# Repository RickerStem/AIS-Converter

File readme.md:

KiCad files and docs for the AIS-Converter project.

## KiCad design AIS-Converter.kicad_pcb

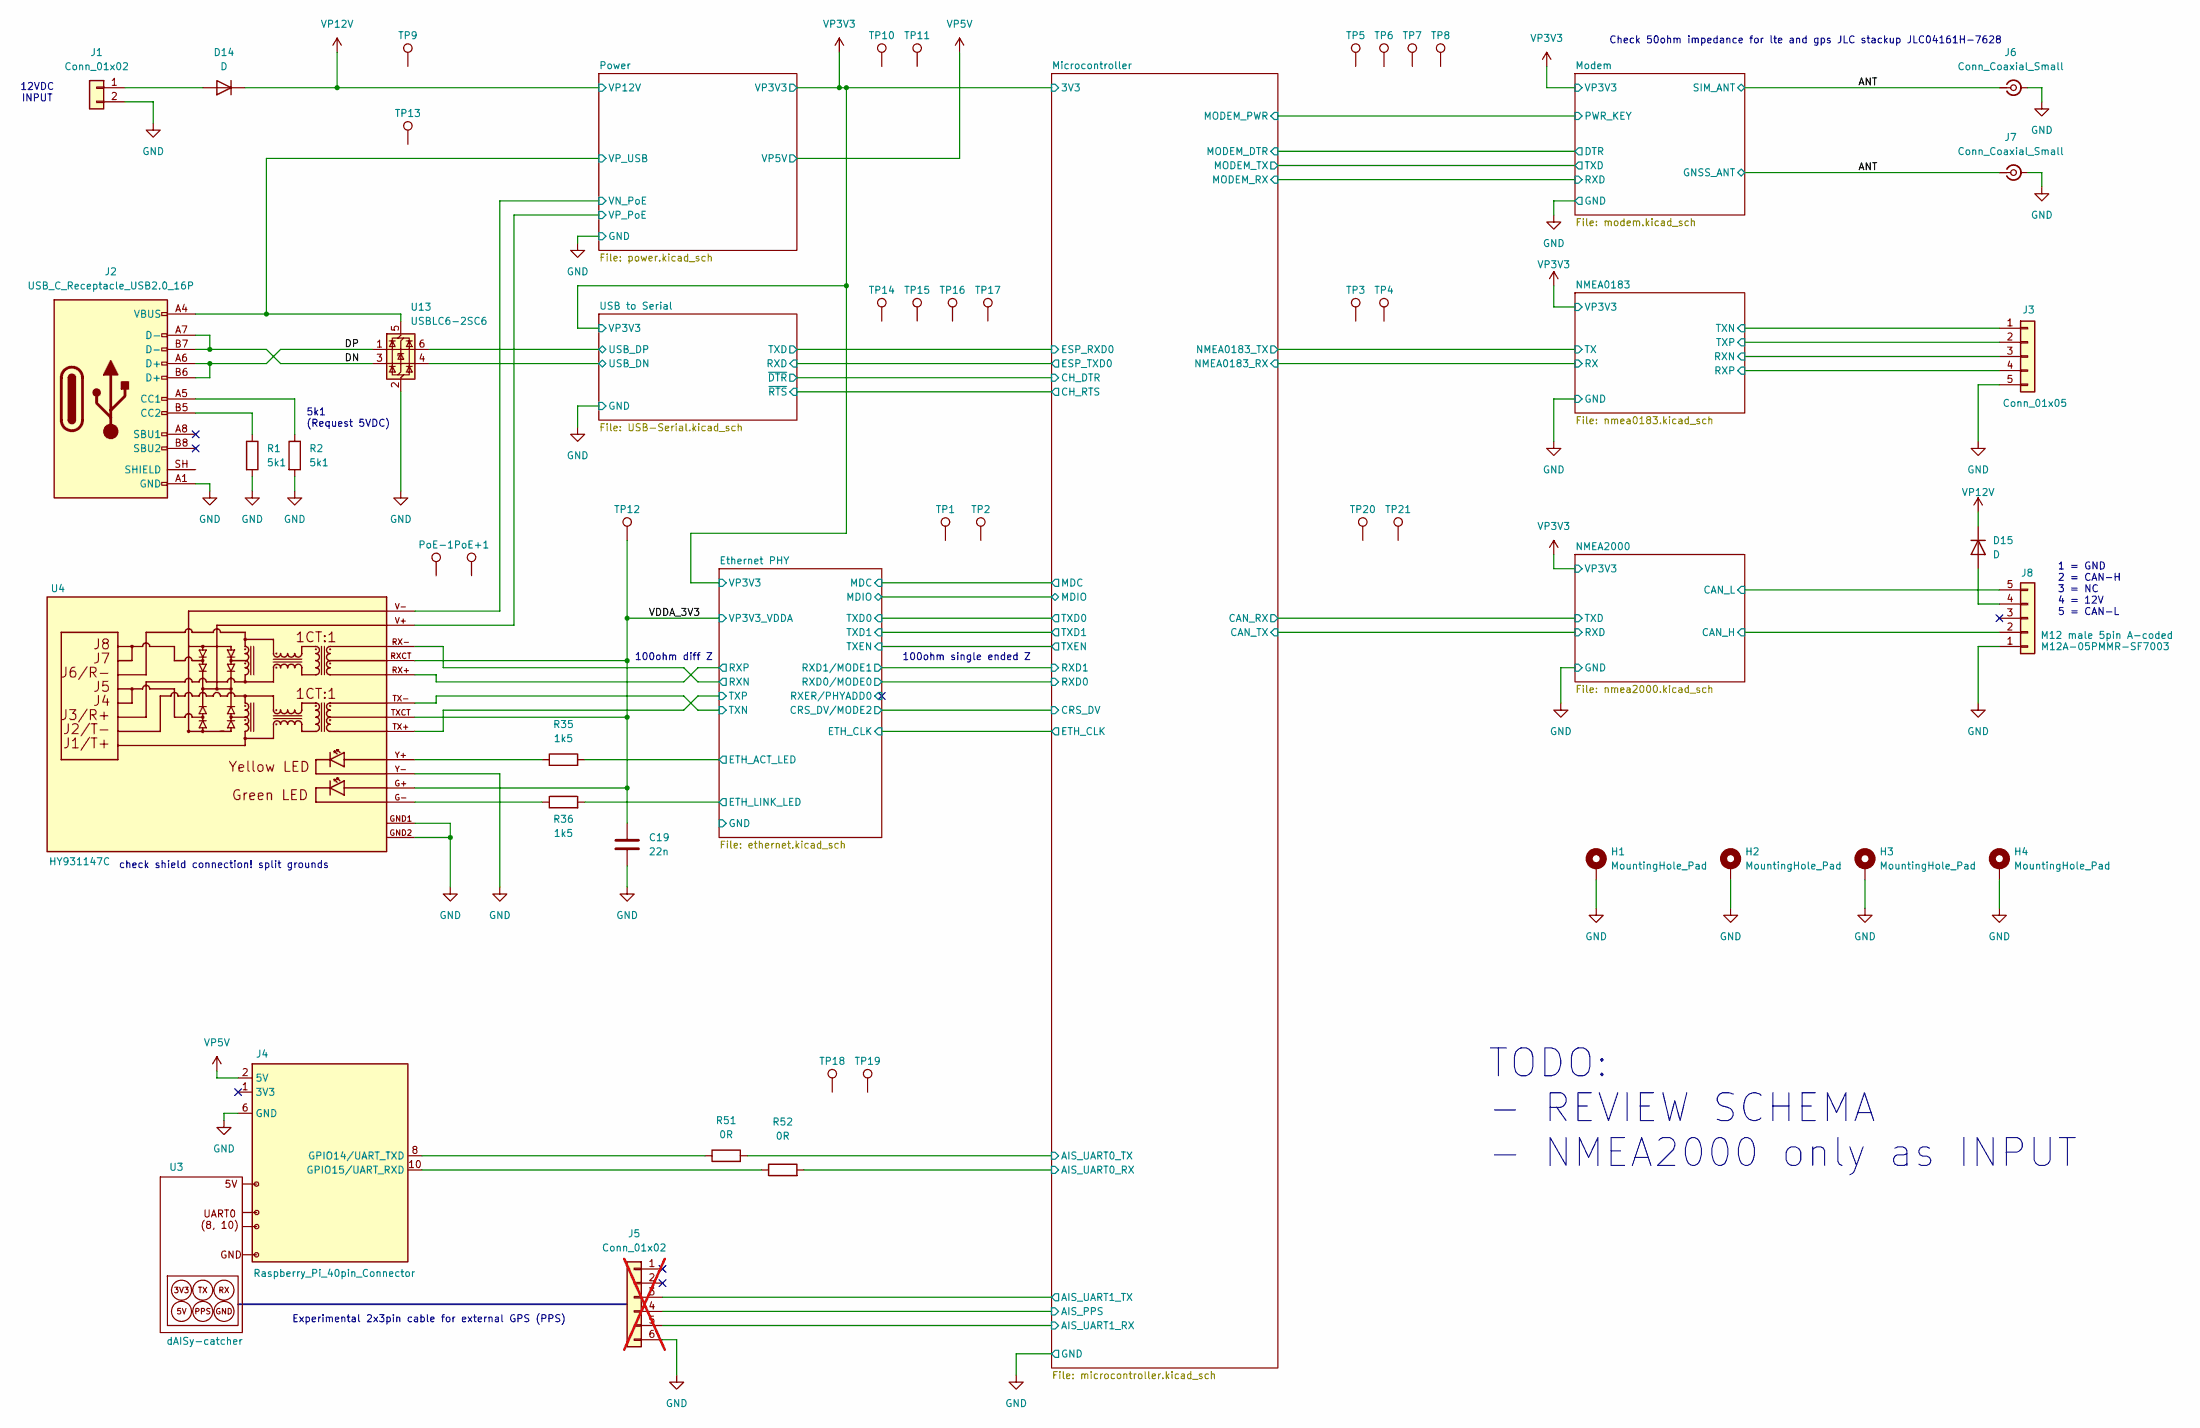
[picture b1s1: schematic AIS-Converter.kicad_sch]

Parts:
C19: 22n; C_0603_1608Metric
D14, D15: D; D_1206_3216Metric
H1, H2, H3, H4: MountingHole_Pad; MountingHole_3.2mm_M3_DIN965_Pad
J1: Conn_01x02; J_Wurth_WR-TBL_691322110002
J2: USB_C_Receptacle_USB2.0_16P; USB_C_Receptacle_Amphenol_124019772112A
J3: Conn_01x05; J_Wurth_WR-TBL_691322110005
J4: Raspberry_Pi_40pin_Connector; PinHeader_2x20_P2.54mm_Vertical
J5: Conn_01x02; PinSocket_2x03_P2.54mm_Vertical; not fitted
J6, J7: Conn_Coaxial_Small; SMA-KWE_C7498154
J8: M12A-05PMMR-SF7003; M12A05PMMRSF7003
PoE+1: TestPoint; TestPoint_Pad_D1.5mm
PoE-1: TestPoint; TestPoint_Pad_D1.5mm
R1, R2: 5k1; R_0805_2012Metric
R35, R36: 1k5; R_0603_1608Metric
R51, R52: 0R; R_0603_1608Metric
TP1, TP2, TP3, TP4, TP5, TP6, TP7, TP8, TP9, TP10, TP11, TP12, TP13, TP14, TP15, TP16, TP17, TP18, TP19, TP20, TP21: TestPoint; TestPoint_Pad_D1.5mm
U3: dAISy-catcher; dAISy-catcher-11mm
U4: HY931147C
U13: USBLC6-2SC6; SOT-23-6

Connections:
/ANT: J6.5 (In), J7.5 (In); also elsewhere on the board
/DN: J2.A7 (D-), J2.B7 (D-), U13.3 (I/O2)
/DP: J2.A6 (D+), J2.B6 (D+), U13.1 (I/O1)
/Ethernet PHY/ETH_ACT_LED: R35.2; also elsewhere on the board
/Ethernet PHY/ETH_LINK_LED: R36.2; also elsewhere on the board
/Ethernet PHY/RXN: U4.RX-; also elsewhere on the board
/Ethernet PHY/RXP: U4.RX+; also elsewhere on the board
/Ethernet PHY/TXN: U4.TX-; also elsewhere on the board
/Ethernet PHY/TXP: U4.TX+; also elsewhere on the board
/Microcontroller/AIS_PPS: J5.4
/Microcontroller/AIS_UART0_RX: R52.2; also elsewhere on the board
/Microcontroller/AIS_UART0_TX: R51.2; also elsewhere on the board
/Microcontroller/AIS_UART1_RX: J5.5
/Microcontroller/AIS_UART1_TX: J5.3
/NMEA0183/RXN: J3.3; also elsewhere on the board
/NMEA0183/RXP: J3.4; also elsewhere on the board
/NMEA0183/TXN: J3.1; also elsewhere on the board
/NMEA0183/TXP: J3.2; also elsewhere on the board
/NMEA2000/CAN_H: J8.2; also elsewhere on the board
/NMEA2000/CAN_L: J8.5; also elsewhere on the board
/Power/VN_PoE: U4.V-; also elsewhere on the board
/Power/VP_PoE: U4.V+; also elsewhere on the board
/Power/VP_USB: J2.A4 (VBUS), J2.A9 (VBUS), J2.B4 (VBUS), J2.B9 (VBUS), U13.5 (VBUS); also elsewhere on the board
/USB to Serial/USB_DN: U13.4 (I/O2); also elsewhere on the board
/USB to Serial/USB_DP: U13.6 (I/O1); also elsewhere on the board
/VDDA_3V3: C19.1, TP12.1 (1_1), U4.G+, U4.RXCT, U4.TXCT; also elsewhere on the board
GND: C19.2, H1.1 (1_1), H2.1 (1_1), H3.1 (1_1), H4.1 (1_1), J1.2, J2.A1 (GND), J2.A12 (GND), J2.B1 (GND), J2.B12 (GND), J3.5, J4.6 (GND), J4.9 (GND), J4.14 (GND), J4.20 (GND), J4.25 (GND), J4.30 (GND), J4.34 (GND), J4.39 (GND), J5.6, J6.1 (Ext), J6.2 (Ext), J6.3 (Ext), J6.4 (Ext), J7.1 (Ext), J7.2 (Ext), J7.3 (Ext), J7.4 (Ext), J8.1, R1.2, R2.2, U4.GND1, U4.GND2, U4.Y-, U13.2 (GND); also elsewhere on the board
unnamed: D14.2 (A), J1.1
unnamed: D15.2 (A), J8.4
unnamed: J2.A5 (CC1), R2.1
unnamed: J2.B5 (CC2), R1.1
unnamed: J4.8 (GPIO14/UART_TXD), R51.1
unnamed: J4.10 (GPIO15/UART_RXD), R52.1
unnamed: R35.1, U4.Y+
unnamed: R36.1, U4.G-
VP5V: J4.2 (5V), J4.4 (5V); also elsewhere on the board
VP12V: D14.1 (K), D15.1 (K)

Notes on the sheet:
12VDC INPUT
100ohm diff Z
check shield connection! split grounds
TODO: - REVIEW SCHEMA - NMEA2000 only as INPUT
Check 50ohm impedance for lte and gps JLC stackup JLC04161H-7628
Experimental 2x3pin cable for external GPS (PPS)
5k1 (Request 5VDC)
100ohm single ended Z
1 = GND 2 = CAN-H 3 = NC 4 = 12V 5 = CAN-L

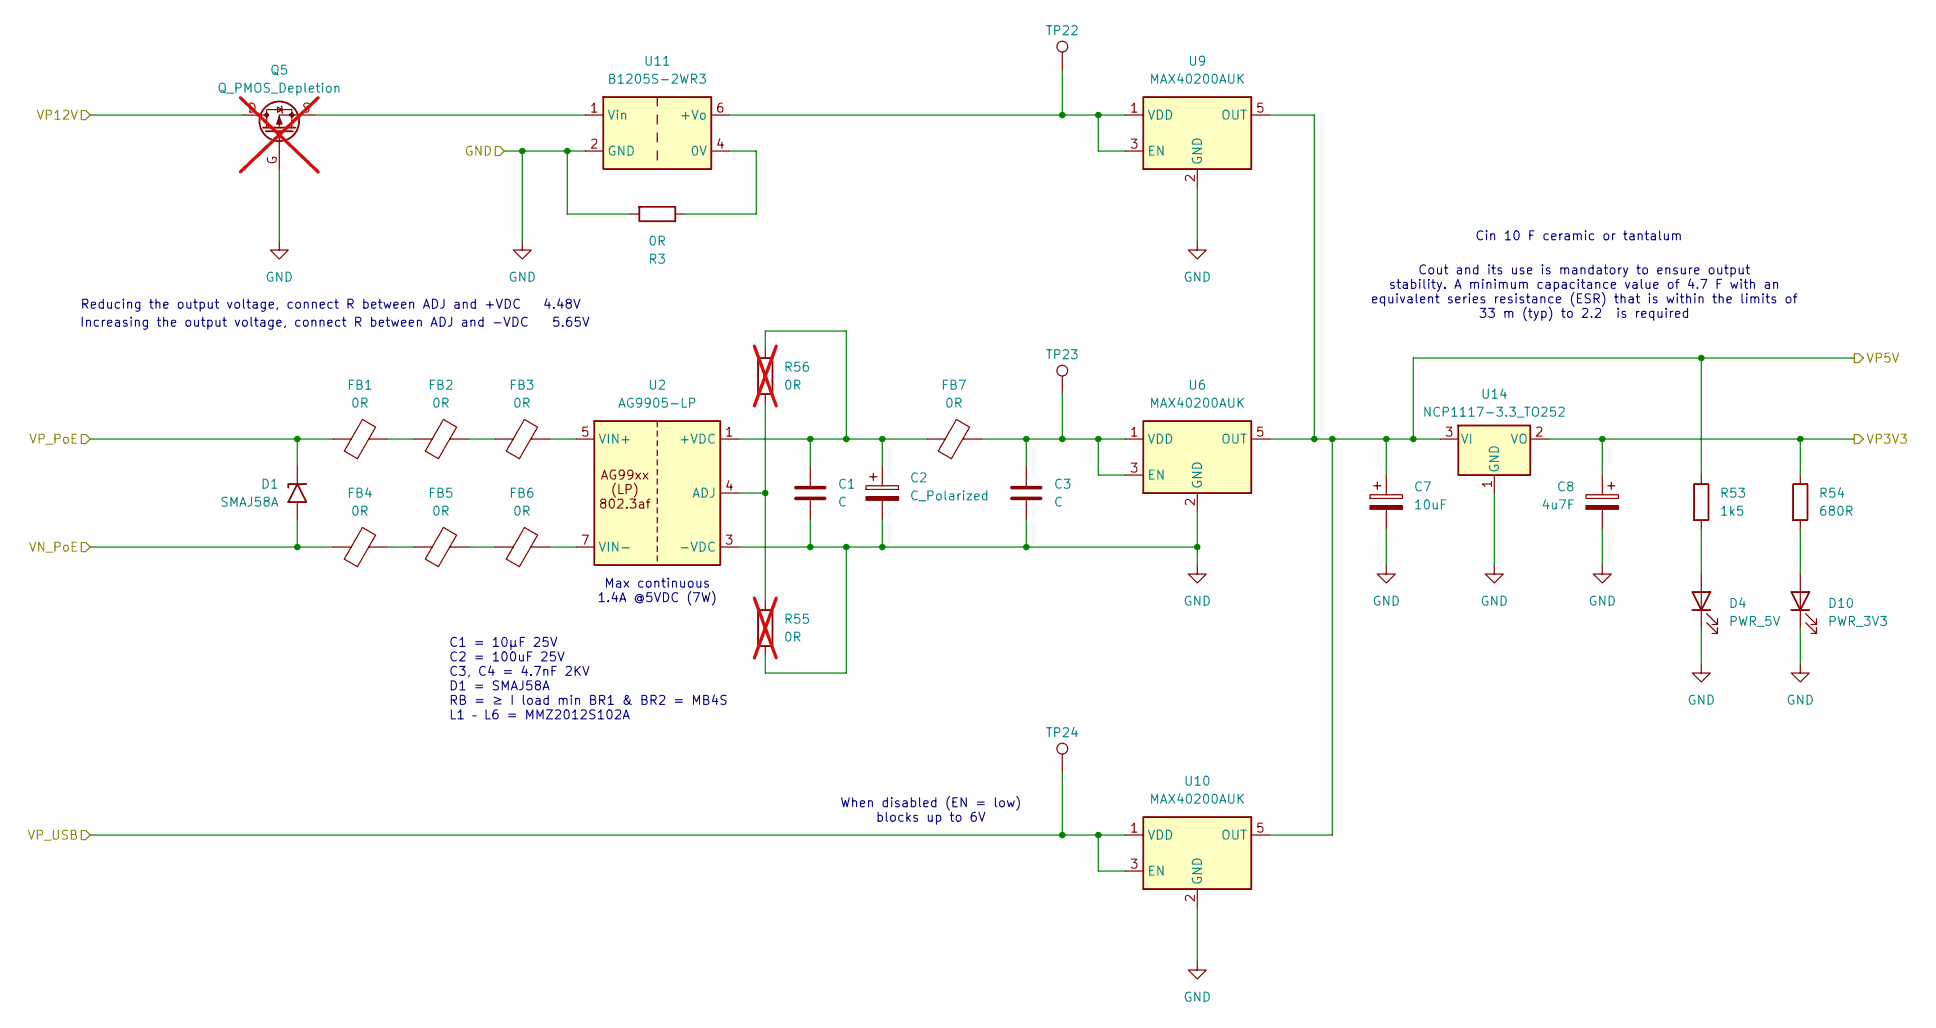
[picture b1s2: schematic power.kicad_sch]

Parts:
C1, C3: C; C_0603_1608Metric
C2: C_Polarized; C_0603_1608Metric
C7: 10uF; C_0603_1608Metric
C8: 4u7F; C_0603_1608Metric
D1: SMAJ58A; D_SMA
D4: PWR_5V; LED_0603_1608Metric
D10: PWR_3V3; LED_0603_1608Metric
FB1, FB2, FB3, FB4, FB5, FB6, FB7: 0R; L_0603_1608Metric
Q5: Q_PMOS_Depletion; not fitted
R3: 0R; R_0201_0603Metric
R53: 1k5; R_0603_1608Metric
R54: 680R; R_0603_1608Metric
R55, R56: 0R; R_0603_1608Metric; not fitted
TP22, TP23, TP24: TestPoint; TestPoint_Pad_D1.5mm
U2: AG9905-LP
U6, U9, U10: MAX40200AUK; SOT-23-5
U11: B1205S-2WR3
U14: NCP1117-3.3_TO252; TO-252-2

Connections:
/Power/VN_PoE: D1.2 (A2), FB4.1; also elsewhere on the board
/Power/VP_PoE: D1.1 (A1), FB1.1; also elsewhere on the board
/Power/VP_USB: TP24.1 (1_1), U10.1 (VDD), U10.3 (EN); also elsewhere on the board
GND: C1.2, C2.2, C3.2, C7.2, C8.2, D4.1 (K), D10.1 (K), Q5.G, R3.2, R55.2, U2.3 (-VDC), U6.2 (GND), U9.2 (GND), U10.2 (GND), U11.2 (GND), U14.1 (GND); also elsewhere on the board
unnamed: C1.1, C2.1, FB7.1, R56.1, U2.1 (+VDC), U2.2 (+VDC)
unnamed: D4.2 (A), R53.2
unnamed: D10.2 (A), R54.2
unnamed: FB1.2, FB2.1
unnamed: FB2.2, FB3.1
unnamed: FB4.2, FB5.1
unnamed: FB5.2, FB6.1
unnamed: R55.1, R56.2, U2.4 (ADJ)
unnamed: C3.1, FB7.2, TP23.1 (1_1), U6.1 (VDD), U6.3 (EN)
unnamed: R3.1, U11.4 (0V)
unnamed: TP22.1 (1_1), U9.1 (VDD), U9.3 (EN), U11.6 (+Vo)
unnamed: Q5.S, U11.1 (Vin)
VIN+: FB3.2, U2.5 (VIN+), U2.6 (VIN+)
VIN-: FB6.2, U2.7 (VIN-), U2.8 (VIN-)
VP3V3: C8.1, R54.1, U14.2 (VO); also elsewhere on the board
VP5V: C7.1, R53.1, U6.5 (OUT), U9.5 (OUT), U10.5 (OUT), U14.3 (VI); also elsewhere on the board

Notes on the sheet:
4.48V
5.65V
Max continuous 1.4A @5VDC (7W)
Cin 10 F ceramic or tantalum
Cout and its use is mandatory to ensure output stability. A minimum capacitance value of 4.7 F with an equivalent series resistance (ESR) that is within the limits of 33 m (typ) to 2.2 is required
Increasing the output voltage, connect R between ADJ and -VDC
When disabled (EN = low) blocks up to 6V
C1 = 10µF 25V C2 = 100uF 25V C3, C4 = 4.7nF 2KV D1 = SMAJ58A RB = ≥ I load min BR1 & BR2 = MB4S L1 – L6 = MMZ2012S102A
Reducing the output voltage, connect R between ADJ and +VDC

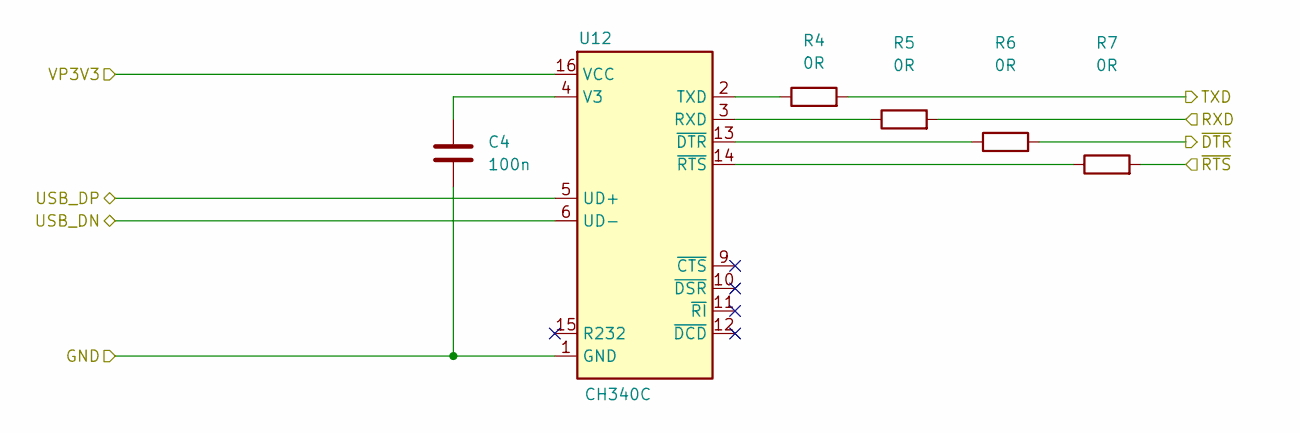
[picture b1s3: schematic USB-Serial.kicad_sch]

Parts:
C4: 100n; C_0603_1608Metric
R4, R5, R6, R7: 0R; R_0603_1608Metric
U12: CH340C; SOIC-16_3.9x9.9mm_P1.27mm

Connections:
/Microcontroller/CH_DTR: R6.2; also elsewhere on the board
/Microcontroller/CH_RTS: R7.2; also elsewhere on the board
/Microcontroller/ESP_RXD0: R4.2; also elsewhere on the board
/Microcontroller/ESP_TXD0: R5.2; also elsewhere on the board
/USB to Serial/USB_DN: U12.6 (UD-); also elsewhere on the board
/USB to Serial/USB_DP: U12.5 (UD+); also elsewhere on the board
GND: C4.2, U12.1 (GND); also elsewhere on the board
unnamed: R5.1, U12.3 (RXD)
unnamed: R4.1, U12.2 (TXD)
unnamed: C4.1, U12.4 (V3)
unnamed: R6.1, U12.13 (~DTR)
unnamed: R7.1, U12.14 (~RTS)
VP3V3: U12.16 (VCC); also elsewhere on the board

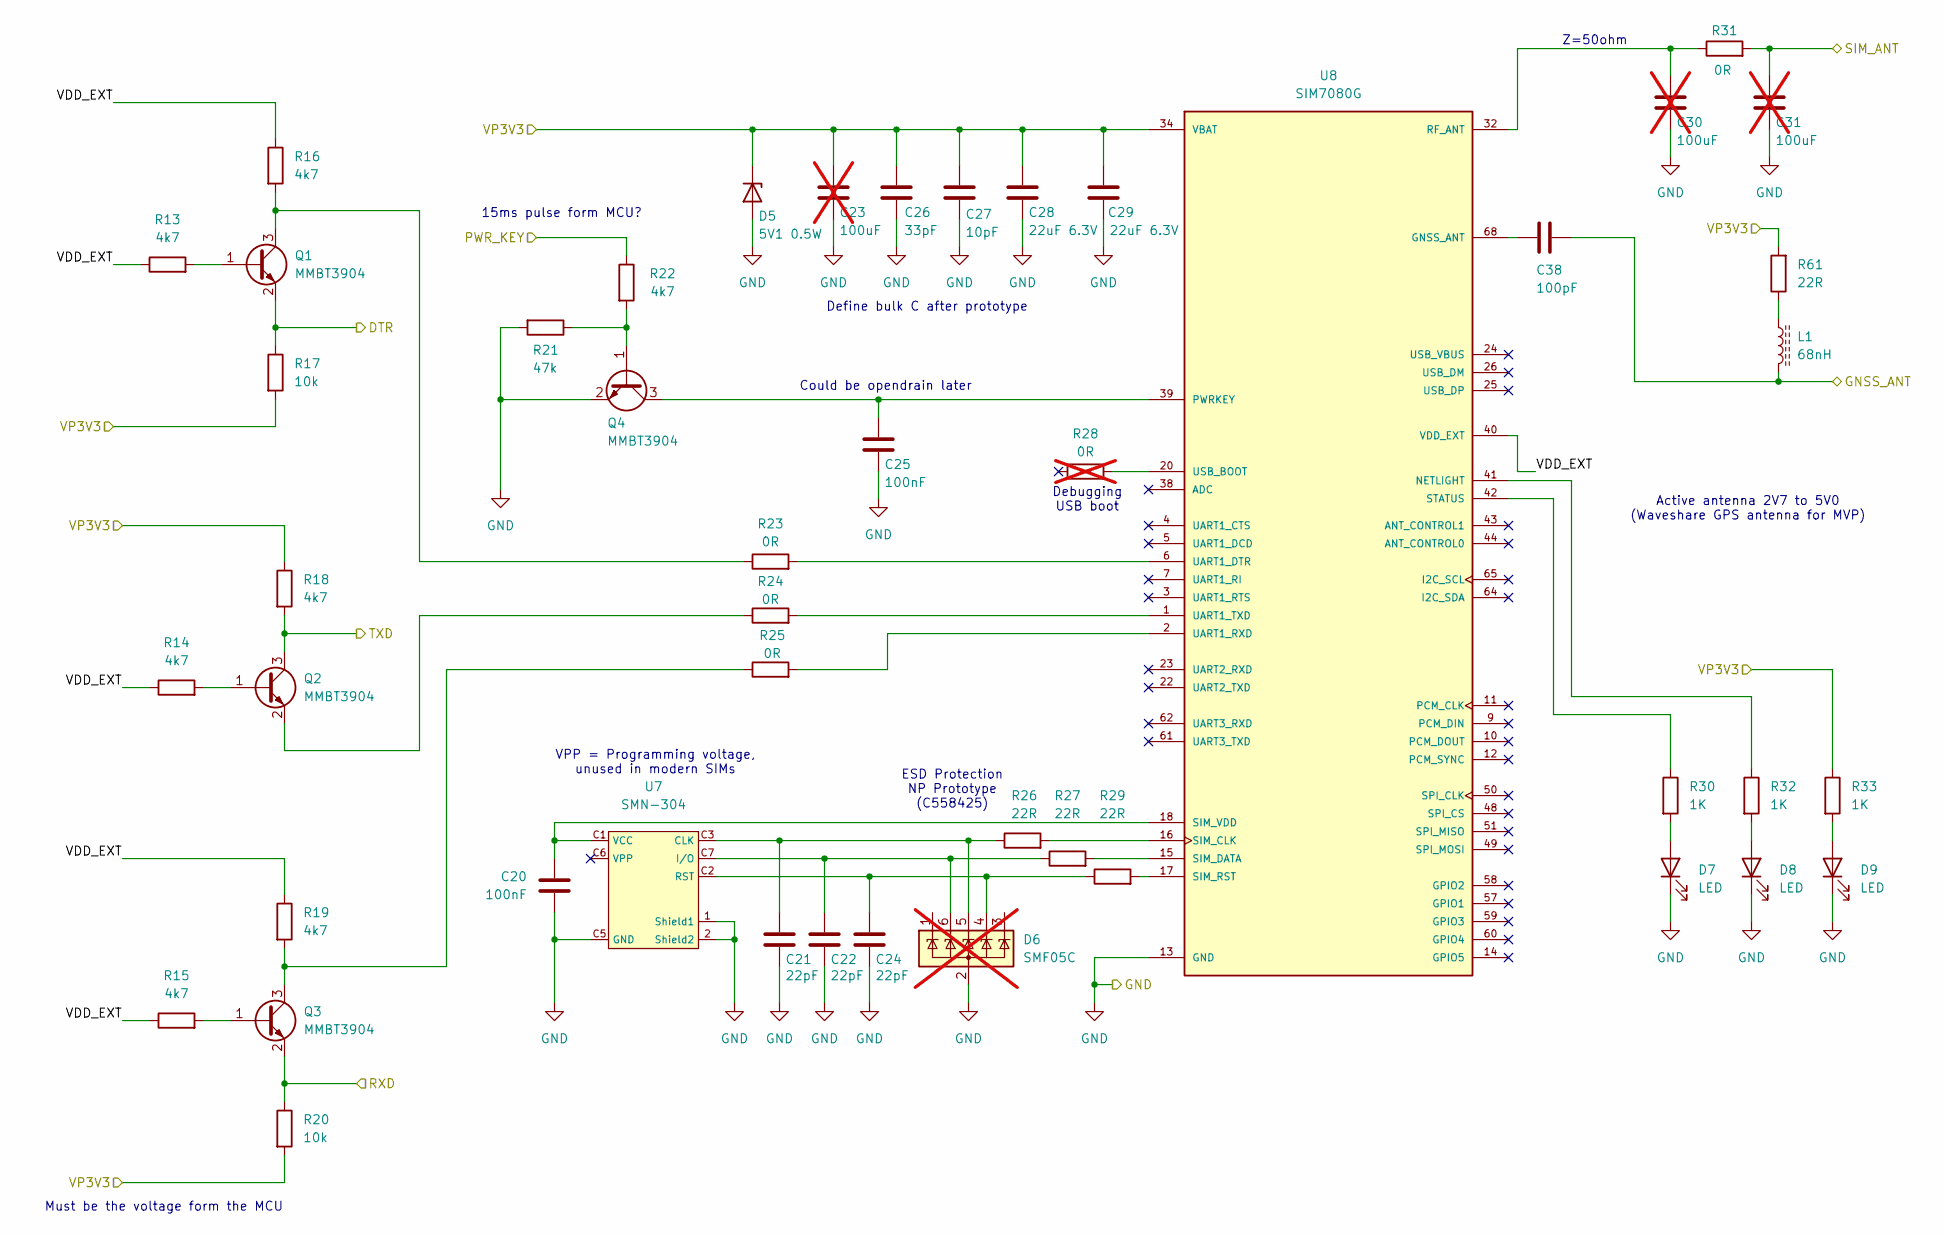
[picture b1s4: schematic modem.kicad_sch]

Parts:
C20, C25: 100nF; C_0603_1608Metric
C21, C22, C24: 22pF; C_0603_1608Metric
C23, C30, C31: 100uF; C_0603_1608Metric; not fitted
C26: 33pF; C_0603_1608Metric
C27: 10pF; C_0603_1608Metric
C28, C29: 22uF 6.3V; C_0603_1608Metric
C38: 100pF; C_0603_1608Metric
D5: 5V1 0.5W; D_MiniMELF
D6: SMF05C; SOT-363_SC-70-6; not fitted
D7, D8, D9: LED; LED_0603_1608Metric
L1: 68nH; L_0603_1608Metric
Q1, Q2, Q3, Q4: MMBT3904; SOT-23
R13, R14, R15, R16, R18, R19, R22: 4k7; R_0603_1608Metric
R17, R20: 10k; R_0603_1608Metric
R21: 47k; R_0603_1608Metric
R23, R24, R25, R31: 0R; R_0603_1608Metric
R26, R27, R29, R61: 22R; R_0603_1608Metric
R28: 0R; R_0603_1608Metric; not fitted
R30, R32, R33: 1K; R_0603_1608Metric
U7: SMN-304; LCSC C266889
U8: SIM7080G; XCVR_SIM7080G; PARTREV 1.04

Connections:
/ANT: C31.1, C38.1, L1.2, R31.2; also elsewhere on the board
/Microcontroller/MODEM_DTR: Q1.2 (E), R17.1; also elsewhere on the board
/Microcontroller/MODEM_PWR: R22.1; also elsewhere on the board
/Microcontroller/MODEM_RX: Q3.2 (E), R20.1; also elsewhere on the board
/Microcontroller/MODEM_TX: Q2.3 (C), R18.2; also elsewhere on the board
/Modem/VDD_EXT: R13.1, R14.1, R15.1, R16.1, R19.1, U8.40 (VDD_EXT)
GND: C20.2, C21.2, C22.2, C23.2, C24.2, C25.2, C26.2, C27.2, C28.2, C29.2, C30.2, C31.2, D5.2 (A), D6.2 (A), D7.1 (K), D8.1 (K), D9.1 (K), Q4.2 (E), R21.2, U7.1 (Shield1), U7.2 (Shield2), U7.C5 (GND), U8.8 (GND), U8.13 (GND), U8.19 (GND), U8.21 (GND), U8.27 (GND), U8.30 (GND), U8.31 (GND), U8.33 (GND), U8.36 (GND), U8.37 (GND), U8.45 (GND), U8.63 (GND), U8.66 (GND), U8.67 (GND), U8.69 (GND), U8.70 (GND), U8.71 (GND), U8.72 (GND), U8.73 (GND), U8.74 (GND), U8.75 (GND), U8.76 (GND), U8.77 (GND); also elsewhere on the board
unnamed: D7.2 (A), R30.2
unnamed: D8.2 (A), R32.2
unnamed: D9.2 (A), R33.2
unnamed: L1.1, R61.1
unnamed: Q1.1 (B), R13.2
unnamed: Q1.3 (C), R16.2, R23.1
unnamed: Q2.1 (B), R14.2
unnamed: Q2.2 (E), R24.1
unnamed: Q3.1 (B), R15.2
unnamed: Q3.3 (C), R19.2, R25.1
unnamed: Q4.1 (B), R21.1, R22.2
unnamed: C25.1, Q4.3 (C), U8.39 (PWRKEY)
unnamed: C21.1, D6.5 (K), R26.1, U7.C3 (CLK)
unnamed: C22.1, D6.6 (K), R27.1, U7.C7 (I/O)
unnamed: C24.1, D6.4 (K), R29.1, U7.C2 (RST)
unnamed: C20.1, U7.C1 (VCC), U8.18 (SIM_VDD)
unnamed: C38.2, U8.68 (GNSS_ANT)
unnamed: R32.1, U8.41 (NETLIGHT)
unnamed: C30.1, R31.1, U8.32 (RF_ANT)
unnamed: R26.2, U8.16 (SIM_CLK)
unnamed: R27.2, U8.15 (SIM_DATA)
unnamed: R29.2, U8.17 (SIM_RST)
unnamed: R30.1, U8.42 (STATUS)
unnamed: R23.2, U8.6 (UART1_DTR)
unnamed: R25.2, U8.2 (UART1_RXD)
unnamed: R24.2, U8.1 (UART1_TXD)
unnamed: R28.2 (~_2), U8.20 (USB_BOOT)
VP3V3: C23.1, C26.1, C27.1, C28.1, C29.1, D5.1 (K), R17.2, R18.1, R20.2, R33.1, R61.2, U8.34 (VBAT), U8.35 (VBAT); also elsewhere on the board

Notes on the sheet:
Define bulk C after prototype
VPP = Programming voltage, unused in modern SIMs
Debugging USB boot
ESD Protection NP Prototype (C558425)
Must be the voltage form the MCU
Z=50ohm
Could be opendrain later
15ms pulse form MCU?
Active antenna 2V7 to 5V0 (Waveshare GPS antenna for MVP)

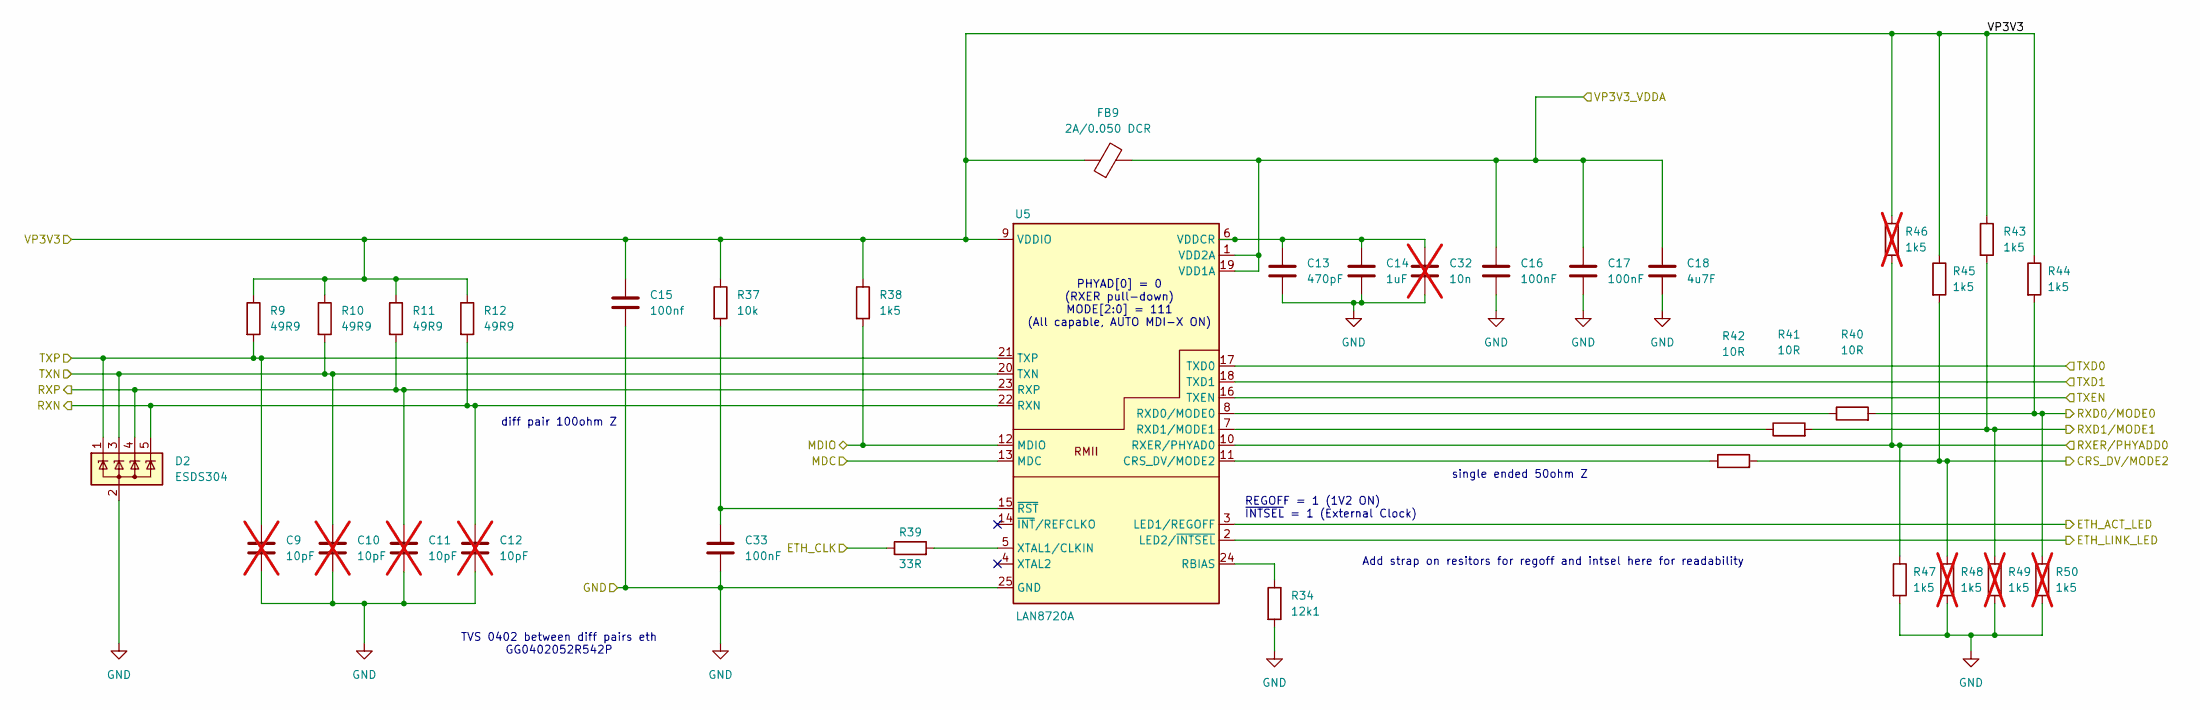
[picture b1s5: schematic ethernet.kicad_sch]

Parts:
C9, C10, C11, C12: 10pF; C_0402_1005Metric; not fitted
C13: 470pF; C_0603_1608Metric
C14: 1uF; C_0603_1608Metric
C15: 100nf; C_0603_1608Metric
C16, C17, C33: 100nF; C_0603_1608Metric
C18: 4u7F; C_0603_1608Metric
C32: 10n; C_0603_1608Metric; not fitted
D2: ESDS304; SOT-23-5
FB9: 2A/0.050 DCR; L_0603_1608Metric
R9, R10, R11, R12: 49R9; R_0402_1005Metric
R34: 12k1; R_0402_1005Metric
R37: 10k; R_0603_1608Metric
R38, R43, R44, R45, R47: 1k5; R_0603_1608Metric
R39: 33R; R_0603_1608Metric
R40, R41, R42: 10R; R_0402_1005Metric
R46, R48, R49, R50: 1k5; R_0603_1608Metric; not fitted
U5: LAN8720A; VQFN-24-1EP_4x4mm_P0.5mm_EP2.5x2.5mm_ThermalVias

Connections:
/Ethernet PHY/CRS_DV/MODE2: R42.2, R45.2, R48.1; also elsewhere on the board
/Ethernet PHY/ETH_ACT_LED: U5.3 (LED1/REGOFF); also elsewhere on the board
/Ethernet PHY/ETH_CLK: R39.1; also elsewhere on the board
/Ethernet PHY/ETH_LINK_LED: U5.2 (LED2/~INTSEL); also elsewhere on the board
/Ethernet PHY/MDC: U5.13 (MDC); also elsewhere on the board
/Ethernet PHY/MDIO: R38.2, U5.12 (MDIO); also elsewhere on the board
/Ethernet PHY/RXD0/MODE0: R40.2, R44.2, R50.1; also elsewhere on the board
/Ethernet PHY/RXD1/MODE1: R41.2, R43.2, R49.1; also elsewhere on the board
/Ethernet PHY/RXER/PHYADD0: R46.2, R47.1, U5.10 (RXER/PHYAD0)
/Ethernet PHY/RXN: C12.1, D2.5 (K), R12.2, U5.22 (RXN); also elsewhere on the board
/Ethernet PHY/RXP: C11.1, D2.4 (K), R11.2, U5.23 (RXP); also elsewhere on the board
/Ethernet PHY/TXD0: U5.17 (TXD0); also elsewhere on the board
/Ethernet PHY/TXD1: U5.18 (TXD1); also elsewhere on the board
/Ethernet PHY/TXEN: U5.16 (TXEN); also elsewhere on the board
/Ethernet PHY/TXN: C10.1, D2.3 (K), R10.2, U5.20 (TXN); also elsewhere on the board
/Ethernet PHY/TXP: C9.1, D2.1 (K), R9.2, U5.21 (TXP); also elsewhere on the board
/VDDA_3V3: C16.1, C17.1, C18.1, FB9.2, U5.1 (VDD2A), U5.19 (VDD1A); also elsewhere on the board
GND: C9.2, C10.2, C11.2, C12.2, C13.2, C14.2, C15.2, C16.2, C17.2, C18.2, C32.2, C33.2, D2.2 (A), R34.2, R47.2, R48.2, R49.2, R50.2, U5.25 (GND); also elsewhere on the board
unnamed: R42.1, U5.11 (CRS_DV/MODE2)
unnamed: R34.1, U5.24 (RBIAS)
unnamed: R40.1, U5.8 (RXD0/MODE0)
unnamed: R41.1, U5.7 (RXD1/MODE1)
unnamed: C13.1, C14.1, C32.1, U5.6 (VDDCR)
unnamed: R39.2, U5.5 (XTAL1/CLKIN)
unnamed: C33.1, R37.2, U5.15 (~RST)
VP3V3: C15.1, FB9.1, R9.1, R10.1, R11.1, R12.1, R37.1, R38.1, R43.1, R44.1, R45.1, R46.1, U5.9 (VDDIO); also elsewhere on the board

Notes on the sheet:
single ended 50ohm Z
PHYAD[0] = 0 (RXER pull-down) MODE[2:0] = 111 (All capable, AUTO MDI-X ON)
diff pair 100ohm Z
TVS 0402 between diff pairs eth GG0402052R542P
Add strap on resitors for regoff and intsel here for readability
REGOFF = 1 (1V2 ON) ~{INTSEL} = 1 (External Clock)

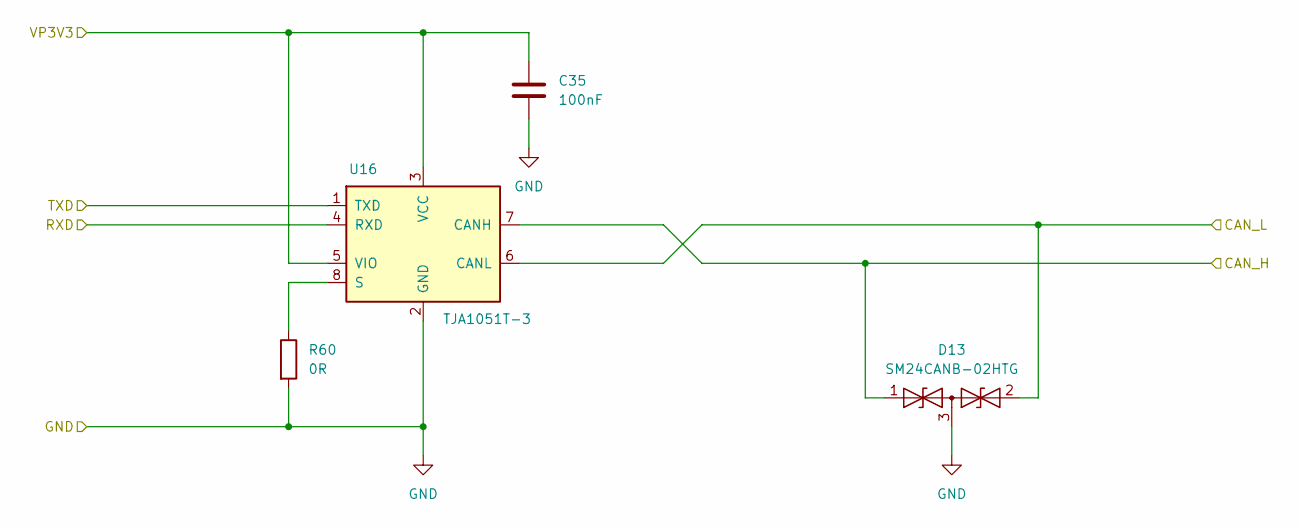
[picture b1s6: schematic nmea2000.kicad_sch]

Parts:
C35: 100nF; C_0603_1608Metric
D13: SM24CANB-02HTG; SOT-23
R60: 0R; R_0603_1608Metric
U16: TJA1051T-3; SOIC-8_3.9x4.9mm_P1.27mm

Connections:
/Microcontroller/CAN_RX: U16.1 (TXD); also elsewhere on the board
/Microcontroller/CAN_TX: U16.4 (RXD); also elsewhere on the board
/NMEA2000/CAN_H: D13.1 (A1), U16.7 (CANH); also elsewhere on the board
/NMEA2000/CAN_L: D13.2 (A2), U16.6 (CANL); also elsewhere on the board
GND: C35.2, D13.3 (common), R60.2, U16.2 (GND); also elsewhere on the board
unnamed: R60.1, U16.8 (S)
VP3V3: C35.1, U16.3 (VCC), U16.5 (VIO); also elsewhere on the board

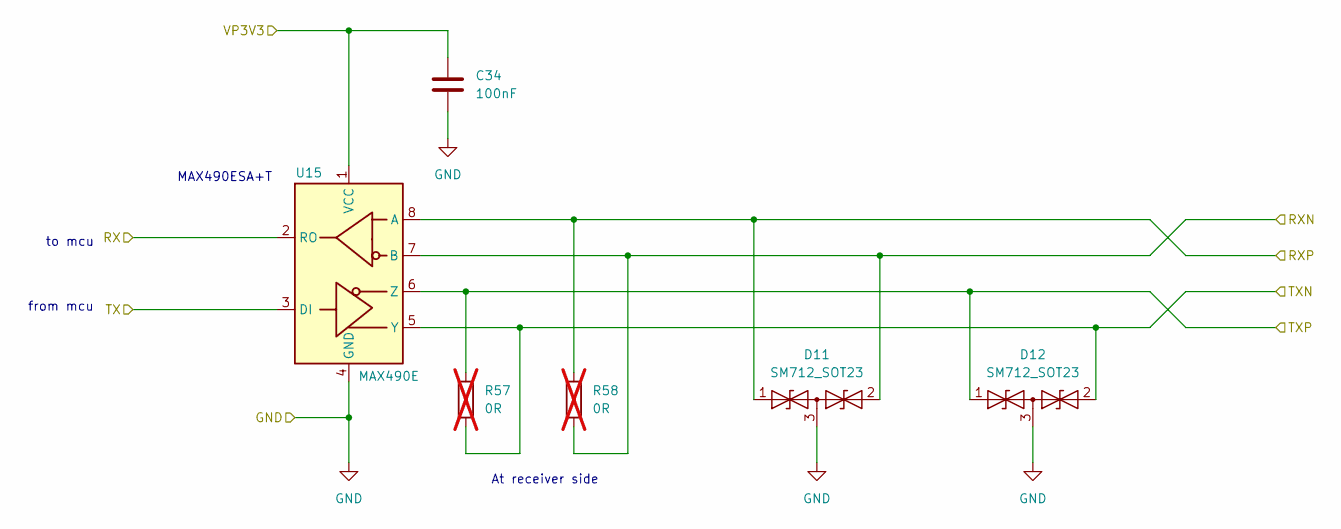
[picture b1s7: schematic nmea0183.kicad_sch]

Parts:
C34: 100nF; C_0603_1608Metric
D11, D12: SM712_SOT23; SOT-23
R57, R58: 0R; R_0603_1608Metric; not fitted
U15: MAX490E; SOIC-8_3.9x4.9mm_P1.27mm

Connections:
/Microcontroller/NMEA0183_RX: U15.2 (RO); also elsewhere on the board
/Microcontroller/NMEA0183_TX: U15.3 (DI); also elsewhere on the board
/NMEA0183/RXN: D11.2 (A2), R58.2, U15.7 (B); also elsewhere on the board
/NMEA0183/RXP: D11.1 (A1), R58.1, U15.8 (A); also elsewhere on the board
/NMEA0183/TXN: D12.2 (A2), R57.2, U15.5 (Y); also elsewhere on the board
/NMEA0183/TXP: D12.1 (A1), R57.1, U15.6 (Z); also elsewhere on the board
GND: C34.2, D11.3 (common), D12.3 (common), U15.4 (GND); also elsewhere on the board
VP3V3: C34.1, U15.1 (VCC); also elsewhere on the board

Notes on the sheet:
from mcu
At receiver side
to mcu
MAX490ESA+T

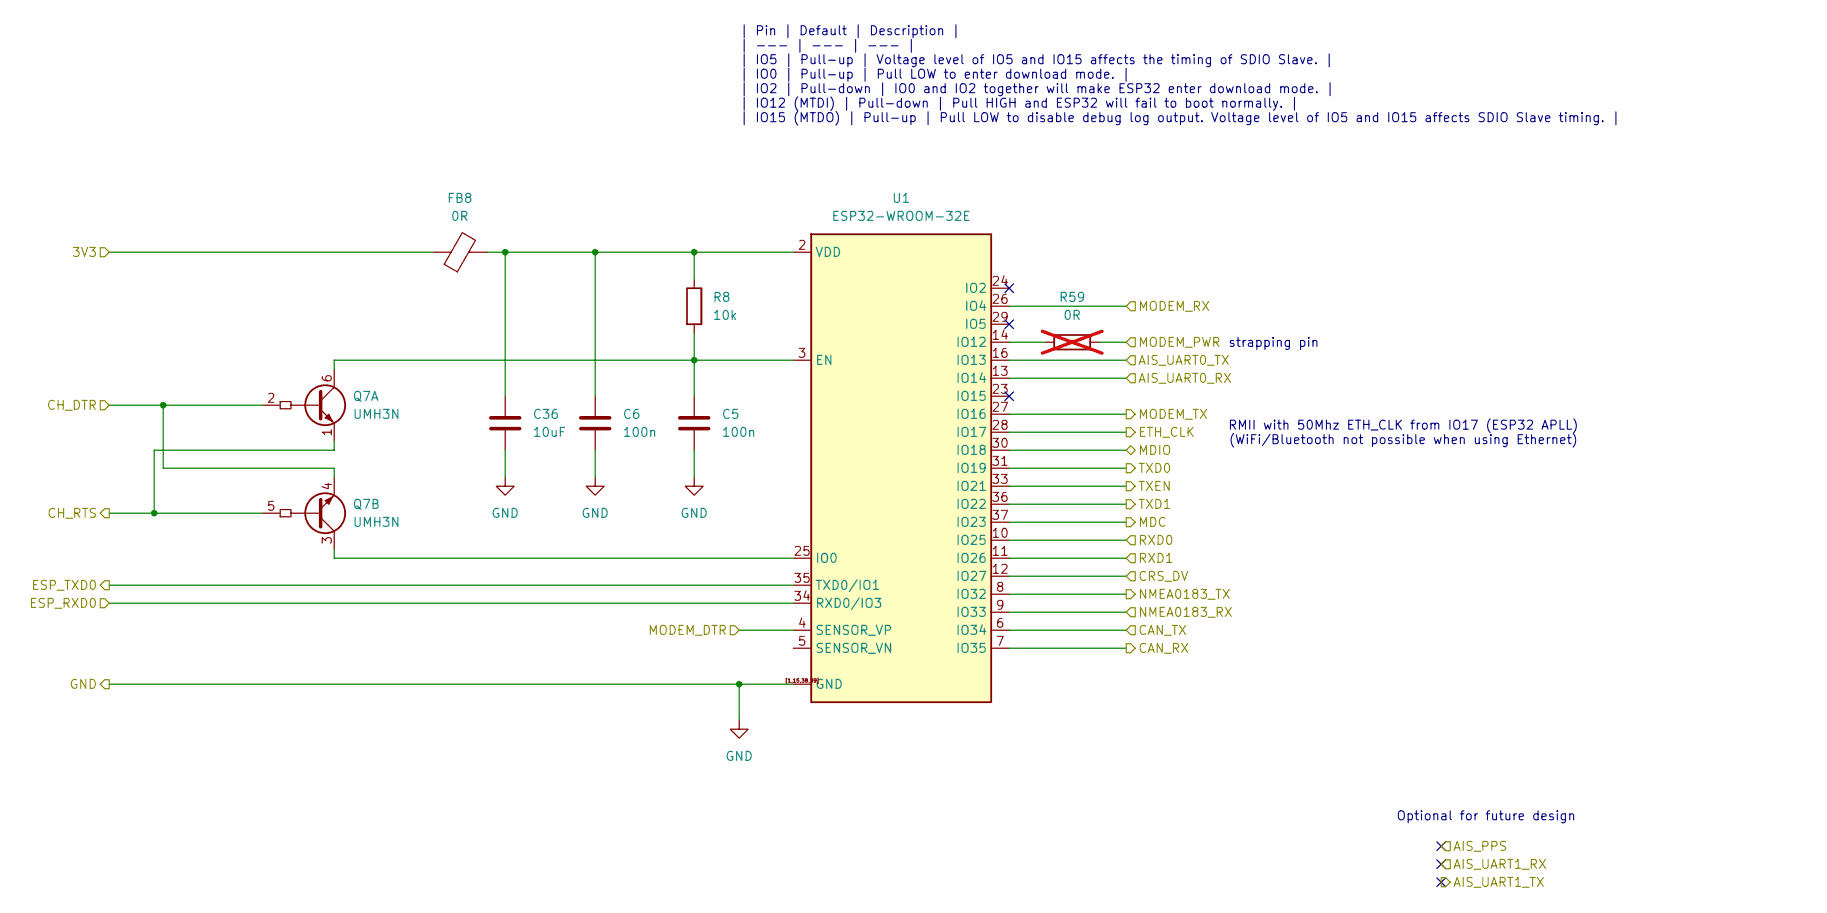
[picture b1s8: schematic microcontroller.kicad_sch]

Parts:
C5, C6: 100n; C_0603_1608Metric
C36: 10uF; C_0603_1608Metric
FB8: 0R; L_0603_1608Metric
Q7: UMH3N; SOT-363_SC-70-6
R8: 10k; R_0603_1608Metric
R59: 0R; R_0603_1608Metric; not fitted
U1: ESP32-WROOM-32E

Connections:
/Ethernet PHY/CRS_DV/MODE2: U1.12 (IO27); also elsewhere on the board
/Ethernet PHY/ETH_CLK: U1.28 (IO17); also elsewhere on the board
/Ethernet PHY/MDC: U1.37 (IO23); also elsewhere on the board
/Ethernet PHY/MDIO: U1.30 (IO18); also elsewhere on the board
/Ethernet PHY/RXD0/MODE0: U1.10 (IO25); also elsewhere on the board
/Ethernet PHY/RXD1/MODE1: U1.11 (IO26); also elsewhere on the board
/Ethernet PHY/TXD0: U1.31 (IO19); also elsewhere on the board
/Ethernet PHY/TXD1: U1.36 (IO22); also elsewhere on the board
/Ethernet PHY/TXEN: U1.33 (IO21); also elsewhere on the board
/Microcontroller/AIS_UART0_RX: U1.13 (IO14); also elsewhere on the board
/Microcontroller/AIS_UART0_TX: U1.16 (IO13); also elsewhere on the board
/Microcontroller/CAN_RX: U1.7 (IO35); also elsewhere on the board
/Microcontroller/CAN_TX: U1.6 (IO34); also elsewhere on the board
/Microcontroller/CH_DTR: Q7.2 (B1), Q7.4 (E2); also elsewhere on the board
/Microcontroller/CH_RTS: Q7.1 (E1), Q7.5 (B2); also elsewhere on the board
/Microcontroller/ESP_RXD0: U1.34 (RXD0/IO3); also elsewhere on the board
/Microcontroller/ESP_TXD0: U1.35 (TXD0/IO1); also elsewhere on the board
/Microcontroller/MODEM_DTR: U1.4 (SENSOR_VP); also elsewhere on the board
/Microcontroller/MODEM_PWR: R59.2; also elsewhere on the board
/Microcontroller/MODEM_RX: U1.26 (IO4); also elsewhere on the board
/Microcontroller/MODEM_TX: U1.27 (IO16); also elsewhere on the board
/Microcontroller/NMEA0183_RX: U1.9 (IO33); also elsewhere on the board
/Microcontroller/NMEA0183_TX: U1.8 (IO32); also elsewhere on the board
GND: C5.2, C6.2, C36.2, U1.1 (GND), U1.15 (GND), U1.38 (GND), U1.39 (GND), U1.[1,15,38,39] (GND); also elsewhere on the board
unnamed: C5.1, Q7.6 (C1), R8.2, U1.3 (EN)
unnamed: Q7.3 (C2), U1.25 (IO0)
unnamed: R59.1, U1.14 (IO12)
unnamed: C6.1, C36.1, FB8.2, R8.1, U1.2 (VDD)
VP3V3: FB8.1; also elsewhere on the board

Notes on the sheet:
| Pin | Default | Description | | --- | --- | --- | | IO5 | Pull-up | Voltage level of IO5 and IO15 affects the timing of SDIO Slave. | | IO0 | Pull-up | Pull LOW to enter download mode. | | IO2 | Pull-down | IO0 and IO2 together will make ESP32 enter download mode. | | IO12 (MTDI) | Pull-down | Pu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
strapping pin
RMII with 50Mhz ETH_CLK from IO17 (ESP32 APLL) (WiFi/Bluetooth not possible when using Ethernet)
Optional for future design
